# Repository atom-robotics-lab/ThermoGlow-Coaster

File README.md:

# Temperature Controlled LED Coaster

This project is an ESP12E based Temperature Controlled Smart Coaster. The project uses the following:
 * ESP12E Module
 * 12 x WS2812B SMD LEDs
 * MLX90614 Temperature Sensor I2C Module
 * Power Bank Charge-Boost Module for charging & boosting 3.7V of Li-Ion cell to 5V.
 * PCB Design was made using KICAD.

 This Project was made in Partnership with [hnhcart.com](https://www.hnhcart.com/) as sponsers and mentors.

 # Schematic

# PCB Design

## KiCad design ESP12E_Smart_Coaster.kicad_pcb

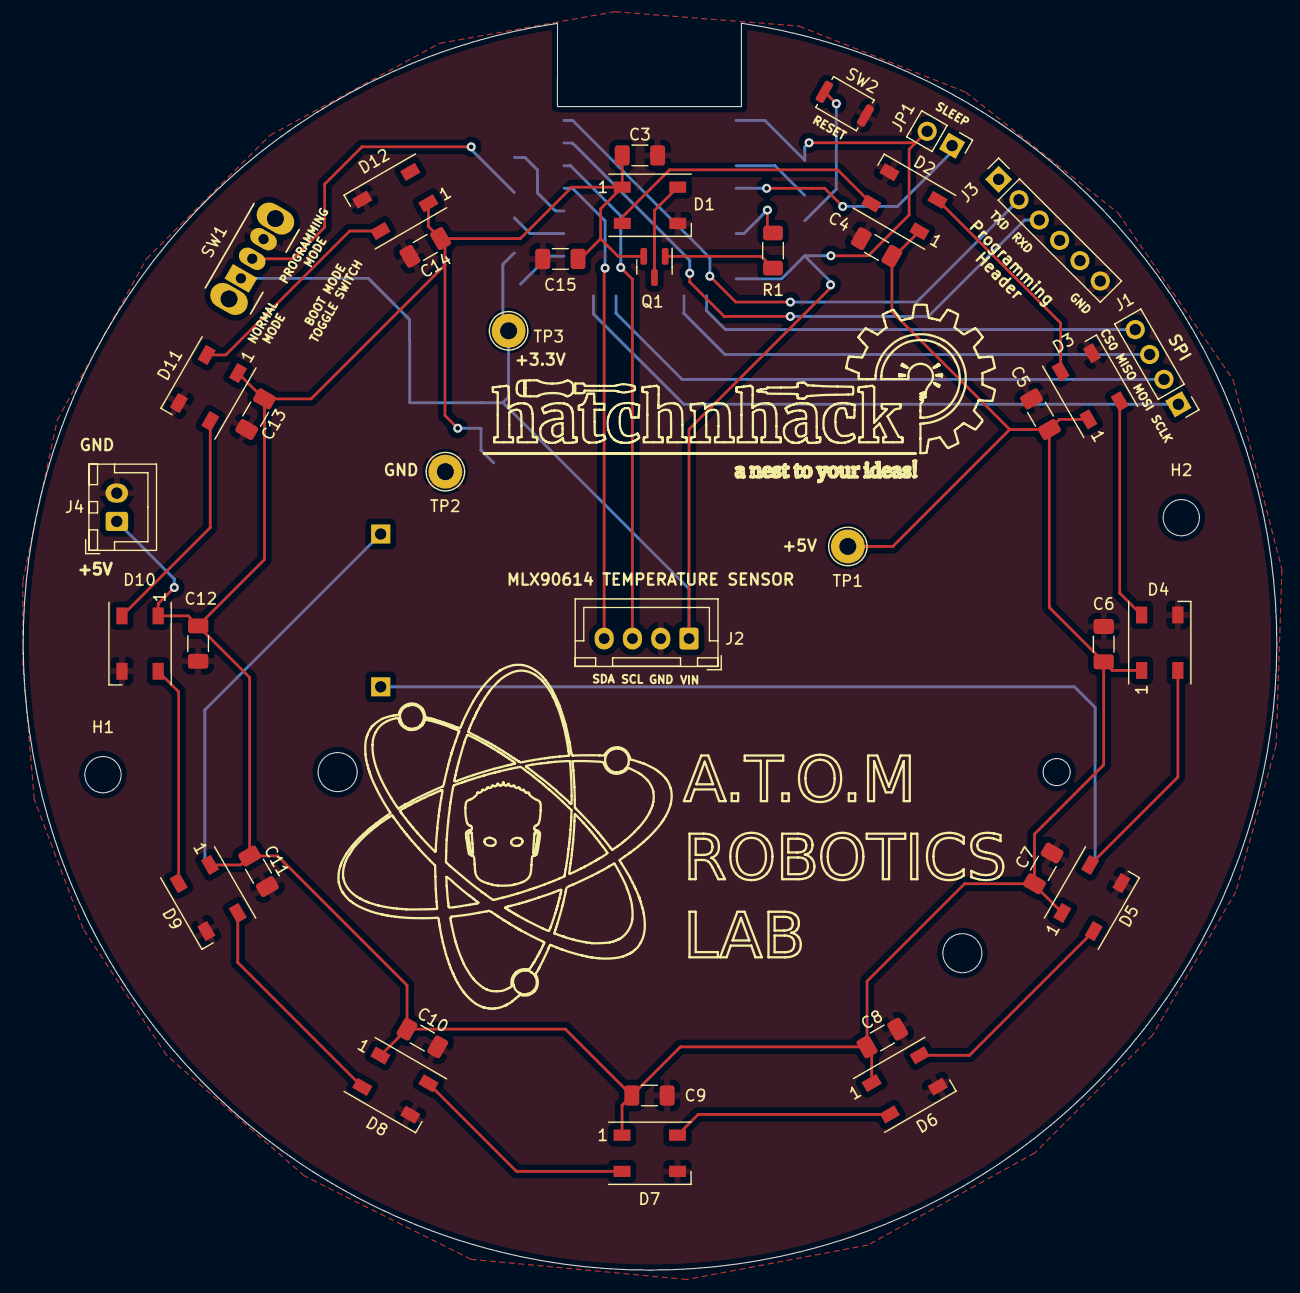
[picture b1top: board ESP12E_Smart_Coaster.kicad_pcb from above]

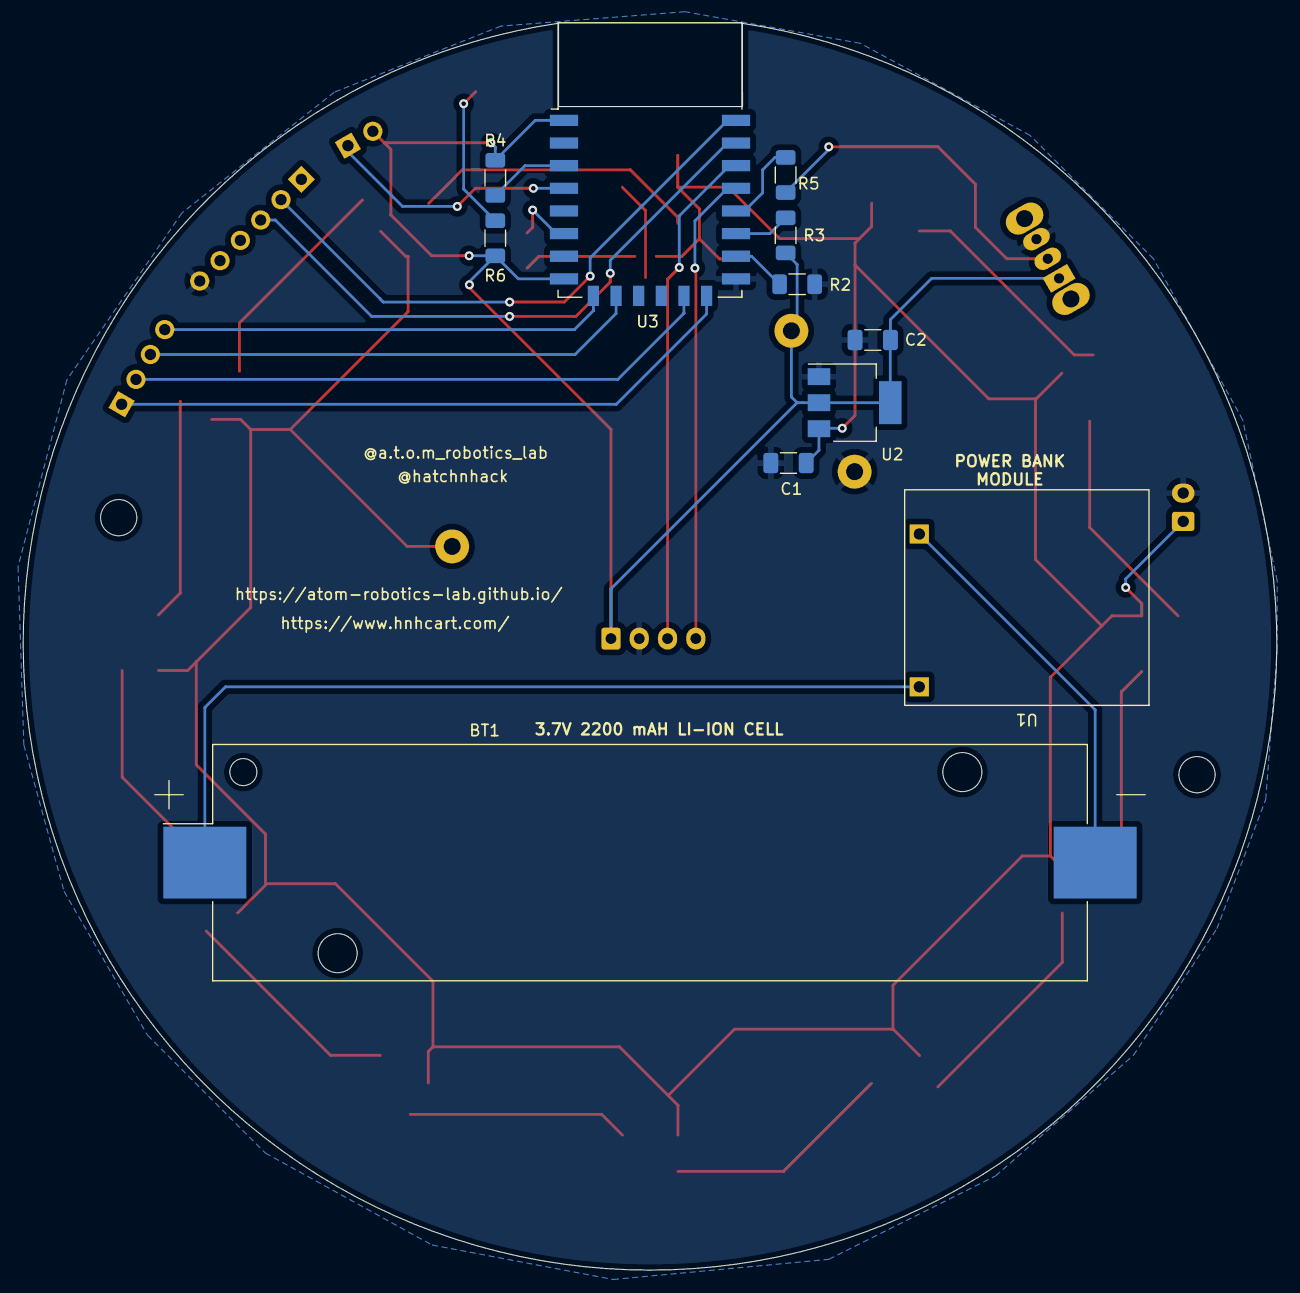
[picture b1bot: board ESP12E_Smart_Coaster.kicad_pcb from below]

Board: 2 copper layers, 110.8 x 110.2 mm, 50 parts (11 on the bottom side), 34 nets.

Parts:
BT1: Battery; BatteryHolder_Keystone_1042_1x18650
C1, C2: 10u; C_1206_3216Metric_Pad1.33x1.80mm_HandSolder
C3, C4, C5, C6, C7, C8, C9, C10, C11, C12, C13, C14: 0.1uF; C_1206_3216Metric_Pad1.33x1.80mm_HandSolder
C15: 100uF; C_1206_3216Metric_Pad1.33x1.80mm_HandSolder
D1, D2, D3, D4, D5, D6, D7, D8, D9, D10, D11, D12: WS2812B; LED_WS2812B_PLCC4_5.0x5.0mm_P3.2mm
H1, H2: MountingHole; MountingHole_3.2mm_M3
J1: SPI_Header; PinHeader_1x04_P2.54mm_Vertical
J2: MLX90614 Temp Sensor; JST_XH_B4B-XH-A_1x04_P2.50mm_Vertical
J3: Programming_header; PinSocket_1x06_P2.54mm_Vertical
J4: Power_Input_Header; JST_XH_B2B-XH-A_1x02_P2.50mm_Vertical
JP1: SolderJumper_2_Open; PinHeader_1x02_P2.54mm_Vertical
Q1: SI2302; SOT-23
R1: 100; R_1206_3216Metric_Pad1.30x1.75mm_HandSolder
R2, R3, R4, R5, R6: 10K; R_1206_3216Metric_Pad1.30x1.75mm_HandSolder
SW1: SW_SPDT; SW_CuK_OS102011MA1QN1_SPDT_Angled
SW2: SW_Push; SW_Push_SPST_NO_Alps_SKRK
TP1: 5V; TestPoint_Loop_D2.54mm_Drill1.5mm_Beaded
TP2: GND; TestPoint_Loop_D2.54mm_Drill1.5mm_Beaded
TP3: 3.3V; TestPoint_Loop_D2.54mm_Drill1.5mm_Beaded
U1: T6845C_Module
U2: AMS1117-3.3; SOT-223-3_TabPin2
U3: ESP-12E

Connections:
+5V: C1.1, C3.1, C4.1, C5.1, C6.1, C7.1, C8.1, C9.1, C10.1, C11.1, C12.1, C13.1, C14.1, C15.1, D1.1 (VDD), D2.1 (VDD), D3.1 (VDD), D4.1 (VDD), D5.1 (VDD), D6.1 (VDD), D7.1 (VDD), D8.1 (VDD), D9.1 (VDD), D10.1 (VDD), D11.1 (VDD), D12.1 (VDD), J4.1, Q1.2, TP1.1, U2.3 (VI)
CS0: J1.4, U3.9 (CS0)
EN/CH_PD: R4.2, U3.3 (EN)
GND: C1.2, C2.2, C3.2, C4.2, C5.2, C6.2, C7.2, C8.2, C9.2, C10.2, C11.2, C12.2, C13.2, C14.2, C15.2, D1.3 (VSS), D2.3 (VSS), D3.3 (VSS), D4.3 (VSS), D5.3 (VSS), D6.3 (VSS), D7.3 (VSS), D8.3 (VSS), D9.3 (VSS), D10.3 (VSS), D11.3 (VSS), D12.3 (VSS), J2.2, J3.6, J4.2, R2.2, SW1.3 (C), SW2.2, TP2.1, U2.1 (GND), U3.15 (GND)
GPIO0: R5.2, U3.18 (GPIO0)
GPIO2: R3.2, U3.17 (GPIO2)
GPIO15: R2.1, U3.16 (GPIO15)
LED_DIN: R1.1, U3.6 (GPIO12)
MISO: J1.3, U3.10 (MISO)
MOSI: J1.2, U3.13 (MOSI)
unnamed: BT1.1 (+), U1.3 (B+)
unnamed: BT1.2 (-), U1.4 (B-)
unnamed: D1.2 (DOUT), D2.4 (DIN)
unnamed: D1.4 (DIN), Q1.3
unnamed: D2.2 (DOUT), D3.4 (DIN)
unnamed: D3.2 (DOUT), D4.4 (DIN)
unnamed: D4.2 (DOUT), D5.4 (DIN)
unnamed: D5.2 (DOUT), D6.4 (DIN)
unnamed: D6.2 (DOUT), D7.4 (DIN)
unnamed: D7.2 (DOUT), D8.4 (DIN)
unnamed: D8.2 (DOUT), D9.4 (DIN)
unnamed: D10.2 (DOUT), D11.4 (DIN)
unnamed: D9.2 (DOUT), D10.4 (DIN)
unnamed: D11.2 (DOUT), D12.4 (DIN)
unnamed: Q1.1, R1.2
unnamed: R5.1, SW1.2 (B)
unnamed: R6.2, SW2.1
RESET: C2.1, J2.1, JP1.2 (B), R3.1, R4.1, R6.1, SW1.1 (A), TP3.1, U2.2 (VO), U3.1 (~RST), U3.8 (VCC)
RXD: J3.3, U3.21 (GPIO3/RXD)
SCL: J2.3, U3.20 (GPIO5)
SCLK: J1.1, U3.14 (SCLK)
SDA: J2.4, U3.19 (GPIO4)
TXD: J3.2, U3.22 (GPIO1/TXD)
WAKE: JP1.1 (A), U3.4 (GPIO16)

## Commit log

2022-05-15 add mc34063AP
2022-05-15 Revert "add mc34063AP"
    This reverts commit ce2e4ae2c6462f3cc229f7f57adec7c62f3c656d.
2022-05-16 add leds
2022-05-20 Deleted eagle files
2022-05-20 Adds .gitignore
2022-05-20 Adds KiCAD files
2022-05-20 add voltage booster
2022-05-20 add components value
2022-05-25 Adds WS2812B Leds & Logic Level Shifter in schematic
2022-05-27 Adds 0.1uF cap to WS2812B LEDs
2022-05-27 Adds library for power bank module and symbol in schematic
2022-08-16 Adds footprints for components
2022-08-19 added footprint for spdt and push switches
2022-08-22 Started component placement
2022-08-22 re-arrange components but not completely done
2022-08-22 Started PCB routing
2022-08-27 Added power connector and wake jumper
2022-08-27 routing changes
2022-08-28 Changed connector positions
2022-08-28 Added images
2022-09-05 Added graphics
2022-09-05 Deleted pcb ss
2022-09-05 Added updated ss
2022-09-09 Added gerber files
2022-09-09 Adds BOM
2023-10-24 Added PCB step file
